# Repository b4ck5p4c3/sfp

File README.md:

## Entering password
```bash
# Writing 4-byte long block data to address 0x7b on DMM (0x51)
i2cset 1 0x51 0x7b 0x00 0x00 0x10 0x11 i
```

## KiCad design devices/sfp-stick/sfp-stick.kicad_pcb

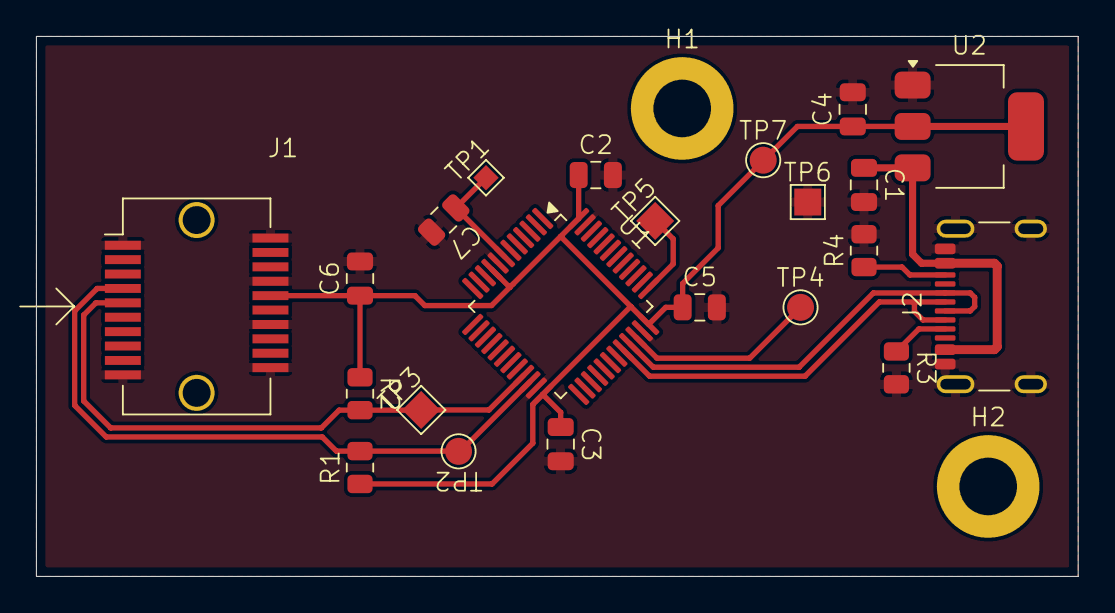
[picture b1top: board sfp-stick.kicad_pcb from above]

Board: 2 copper layers, 57.9 x 30.0 mm, 24 parts (0 on the bottom side), 12 nets.

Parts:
C1, C5: 10uF 16V; C_0805_2012Metric
C2, C3, C4, C6, C7: 0.1uF 6.3V; C_0805_2012Metric
H1, H2: M3; MountingHole_3.2mm_M3_ISO7380_Pad
J1: SFP+; Connector_SFP_NoCage
J2: USB_C_Receptacle_USB2.0_16P; USB_C_Receptacle_GCT_USB4105-xx-A_16P_TopMnt_Horizontal
R1, R2, R3, R4: 5K1; R_0805_2012Metric
TP1: NRST; TestPoint_Pad_1.0x1.0mm
TP2: SDA; TestPoint_Pad_D1.5mm
TP3: SCL; TestPoint_Pad_1.5x1.5mm
TP4: SWDIO; TestPoint_Pad_D1.5mm
TP5: SWCLK; TestPoint_Pad_1.5x1.5mm
TP6: GND; TestPoint_Pad_1.5x1.5mm
TP7: 3V3; TestPoint_Pad_D1.5mm
U1: CH32L103C8T6; LQFP-48_7x7mm_P0.5mm
U2: LT1117-3.3; SOT-223-3_TabPin2

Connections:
+3V3: C2.1, C3.1, C4.1, C5.1, C6.1, J1.16 (VccT), R1.1, R2.1, TP7.1, U1.9 (VDDA), U1.24 (VDD), U1.36 (VDD), U1.48 (VDD), U2.2 (VO)
/SCL: J1.5 (SCL), R2.2, TP3.1, U1.21 (PB10)
/SDA: J1.4 (SDA), R1.2, TP2.1, U1.22 (PB11)
/USB_D+: J2.A6 (D+), J2.B6 (D+), U1.33 (PA12)
/USB_D-: J2.A7 (D-), J2.B7 (D-), U1.32 (PA11)
GND: C1.2, C2.2, C3.2, C4.2, C5.2, C6.2, C7.2, J1.1 (VeeT), J1.10 (VeeR), J1.11 (VeeR), J1.14 (VeeR), J1.17 (VeeT), J1.20 (VeeT), J2.A1 (GND), J2.A12 (GND), J2.B1 (GND), J2.B12 (GND), J2.S1 (SHIELD), R3.2, R4.2, TP6.1, U1.8 (VSSA), U1.23 (VSS), U1.35 (VSS), U1.47 (VSS), U2.1 (GND)
unnamed: J2.A5 (CC1), R3.1
unnamed: J2.B5 (CC2), R4.1
unnamed: C7.1, TP1.1, U1.7 (NRST)
unnamed: TP4.1, U1.34 (PA13)
unnamed: TP5.1, U1.37 (PA14)
VBUS: C1.1, J2.A4 (VBUS), J2.A9 (VBUS), J2.B4 (VBUS), J2.B9 (VBUS), U2.3 (VI)

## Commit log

2025-01-24 Let's build this shitty collection
    Uploading a bunch of dumps. More coming soon, maybe...
2025-05-06 feat: re-arrange repo
2025-05-07 feat: add SFP Stick Rev. A board

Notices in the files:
devices/sfp-stick/sfp-stick.kicad_pcb:
CERN-OHL-S
